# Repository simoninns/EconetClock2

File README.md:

## Synopsis

EconetClock2 is the ATtiny45-20 firmware source code for the EconetClock2 project.

## Motivation

This project creates an Acorn Econet clock suitable for use with Acorn computers from the 1980s and 90s.  The Acorn Econet network is an EIA-422-B based network that is driven by a differential clock signal.

There are several designs for Econet clocks available on the Internet and even a few commercial providers of clocks, however most designs are based-on (or derived from) Acorns original design and require a complex, high-component count circuit in order to operate.

The clock created by this project consists of only 3 primary components (an ATtiny45-20 microcontroller, a capacitor and a resistor) and is therefore much easier to build.

## Installation

Note: This is an AVR Studio 7 project that can be loaded and compiled by the IDE

Please see http://www.waitingforfriday.com/?p=19 for detailed documentation about EconetClock2

## Author

EconetClock2 is written and maintained by Simon Inns.

## License

    EconetClock2 is free software: you can redistribute it and/or modify
    it under the terms of the GNU General Public License as published by
    the Free Software Foundation, either version 3 of the License, or
    (at your option) any later version.

    EconetClock2 is distributed in the hope that it will be useful,
    but WITHOUT ANY WARRANTY; without even the implied warranty of
    MERCHANTABILITY or FITNESS FOR A PARTICULAR PURPOSE.  See the
    GNU General Public License for more details.

    You should have received a copy of the GNU General Public License
    along with EconetClock2. If not, see <http://www.gnu.org/licenses/>.

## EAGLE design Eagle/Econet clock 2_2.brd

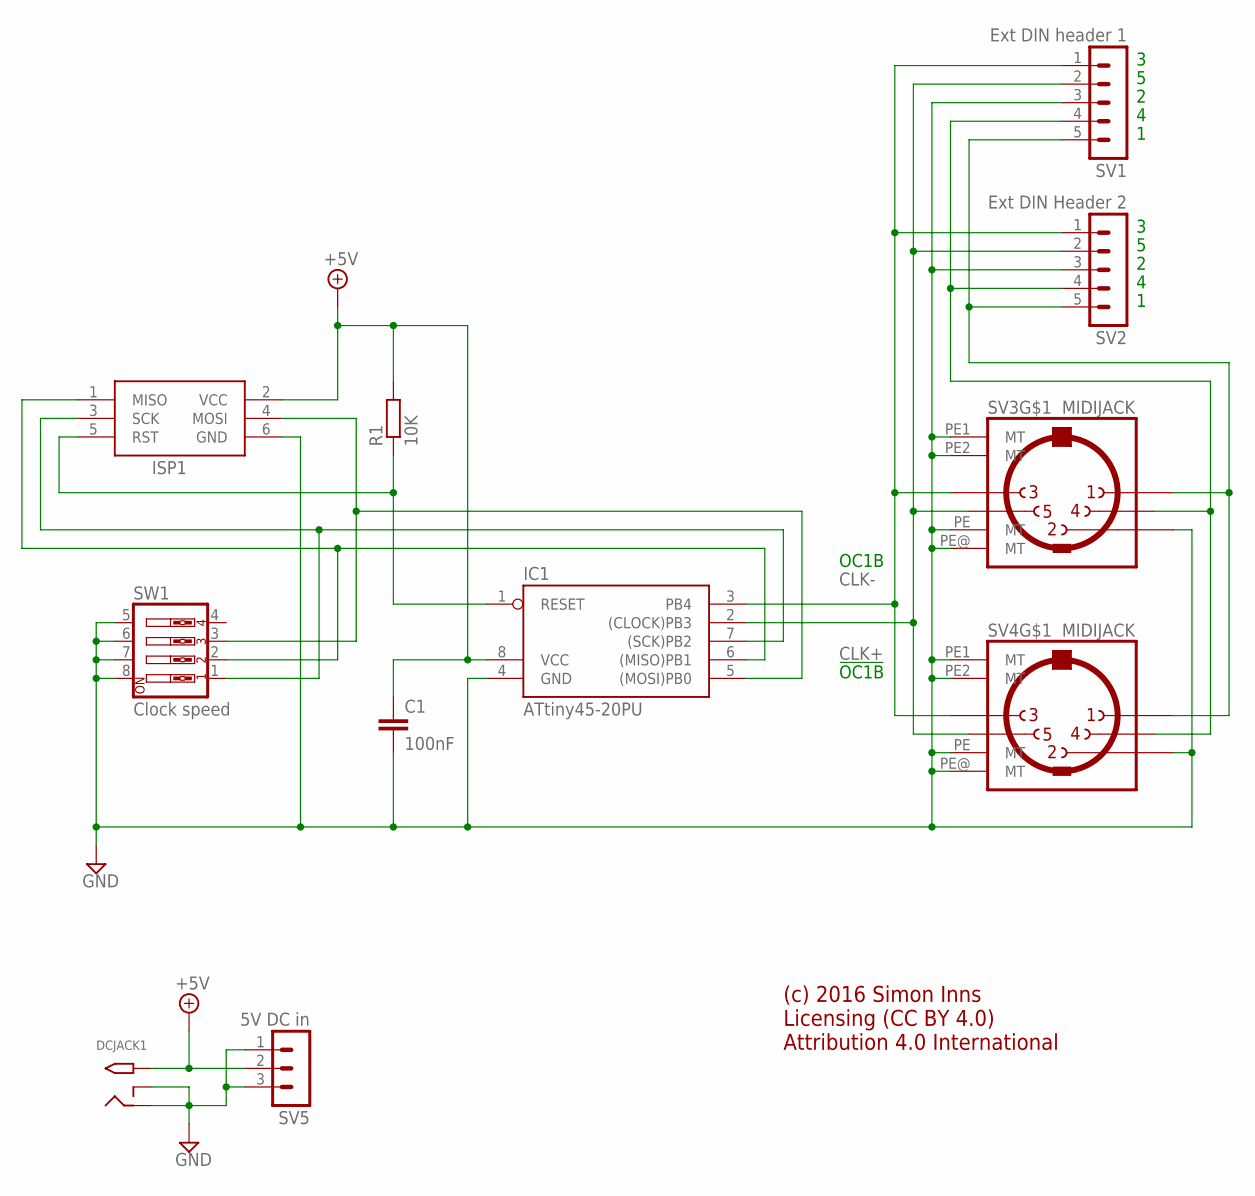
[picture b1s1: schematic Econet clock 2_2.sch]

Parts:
C1: 100nF; C050-025X075
DCJACK1: 5V in; PJ-102A
IC1: ATtiny45-20PU; DIL08
ISP1: AVRISP-6; AVRISP
R1: 10K; 0204/7
SV1: Ext DIN header 1; MA05-1
SV2: Ext DIN Header 2; MA05-1
SV3, SV4: MIDIJACK; CP-2350
SV5: 5V DC in; MA03-1
SW1: Clock speed; EDG-04

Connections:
+5V: C1.1, DCJACK1.TIP, IC1.8 (VCC), ISP1.2 (VCC), R1.2, SV5.2
CLK+: IC1.2 ((CLOCK)PB3), SV1.2, SV2.2, SV3.5, SV4.5
CLK-: IC1.3 (PB4), SV1.1, SV2.1, SV3.3, SV4.3
GND: C1.2, DCJACK1.RING, DCJACK1.RING_SW, IC1.4 (GND), ISP1.6 (GND), SV1.3, SV2.3, SV3.2, SV3.PE (MT), SV3.PE1 (MT), SV3.PE2 (MT), SV3.PE@ (MT), SV4.2, SV4.PE (MT), SV4.PE1 (MT), SV4.PE2 (MT), SV4.PE@ (MT), SV5.1, SV5.3, SW1.5, SW1.6, SW1.7, SW1.8
unnamed: IC1.5 ((MOSI)PB0), ISP1.4 (MOSI), SW1.3
unnamed: IC1.7 ((SCK)PB2), ISP1.3 (SCK), SW1.1
unnamed: SV1.4, SV2.4, SV3.4, SV4.4
unnamed: IC1.6 ((MISO)PB1), ISP1.1 (MISO), SW1.2
unnamed: IC1.1 (RESET), ISP1.5 (RST), R1.1
unnamed: SV1.5, SV2.5, SV3.1, SV4.1

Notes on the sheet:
OC1B
!OC1B
(c) 2016 Simon Inns Licensing (CC BY 4.0) Attribution 4.0 International

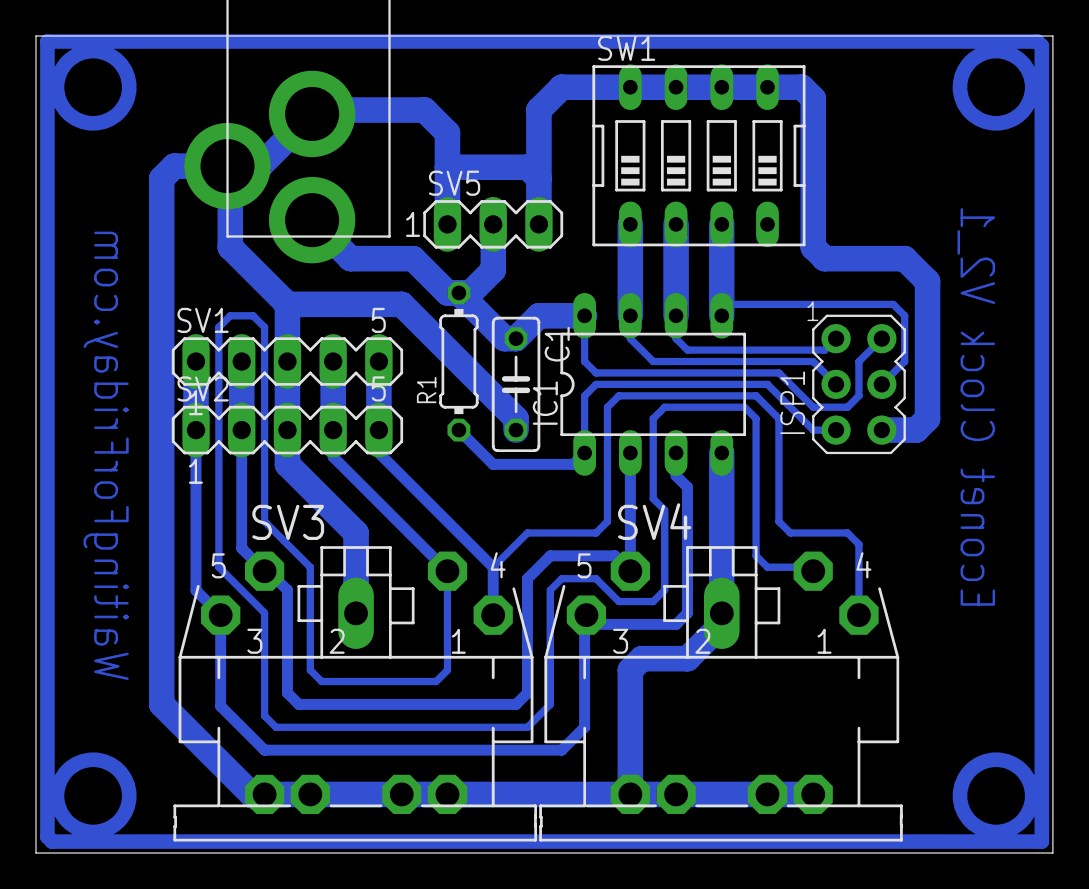
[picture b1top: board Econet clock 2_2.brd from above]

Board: 8 copper layers, 56.5 x 45.4 mm, 11 parts (0 on the bottom side), 10 nets.

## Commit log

2017-02-11 :lollipop: Added .gitattributes & .gitignore files
2017-02-11 Initial commit of Econet Clock 2
    Initial commit of Econet Clock 2
2017-02-11 Added EagleCAD schematic and board files for project
    Added EagleCAD schematic and board files for project
